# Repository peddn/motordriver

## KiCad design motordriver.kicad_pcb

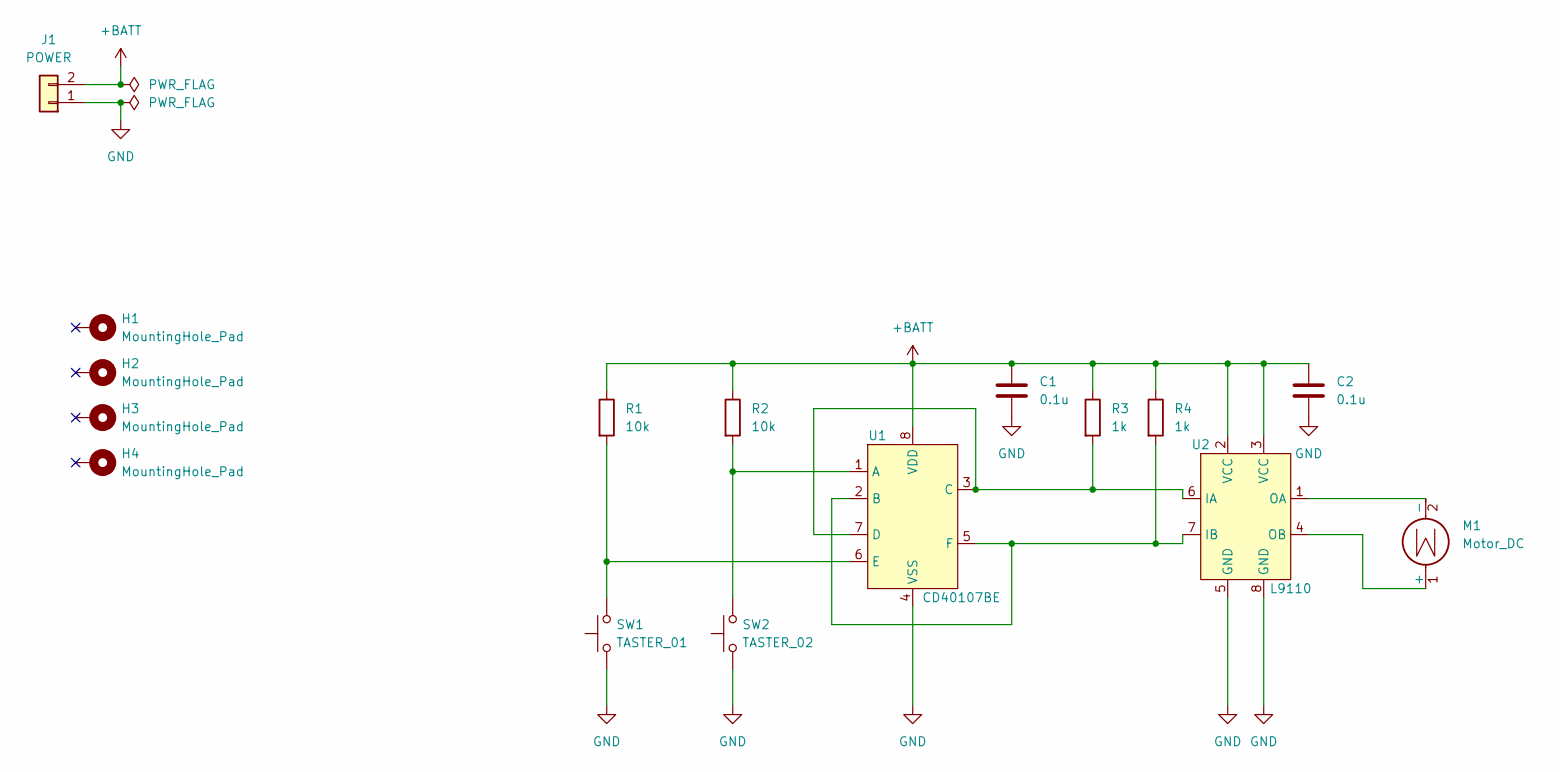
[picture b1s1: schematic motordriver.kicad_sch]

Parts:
C1, C2: 0.1u; C_1206_3216Metric
H1, H2, H3, H4: MountingHole_Pad; MountingHole_3.2mm_M3_Pad_Via
J1: POWER; JST_PH_B2B-PH-K_1x02_P2.00mm_Vertical
M1: Motor_DC; JST_PH_B2B-PH-K_1x02_P2.00mm_Vertical
R1, R2: 10k; R_1206_3216Metric
R3, R4: 1k; R_1206_3216Metric
SW1: TASTER_01; JST_PH_B2B-PH-K_1x02_P2.00mm_Vertical
SW2: TASTER_02; JST_PH_B2B-PH-K_1x02_P2.00mm_Vertical
U1: CD40107BE; DIP-8_W7.62mm_LongPads
U2: L9110; DIP-8_W7.62mm_LongPads

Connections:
+BATT: C1.1, C2.1, J1.2, R1.1, R2.1, R3.1, R4.1, U1.8 (VDD), U2.2 (VCC), U2.3 (VCC)
GND: C1.2, C2.2, J1.1, SW1.1, SW2.1, U1.4 (VSS), U2.5 (GND), U2.8 (GND)
unnamed: M1.1 (+), U2.4 (OB)
unnamed: M1.2 (-), U2.1 (OA)
unnamed: R1.2, SW1.2, U1.6 (E)
unnamed: R2.2, SW2.2, U1.1 (A)
unnamed: R3.2, U1.3 (C), U1.7 (D), U2.6 (IA)
unnamed: R4.2, U1.2 (B), U1.5 (F), U2.7 (IB)

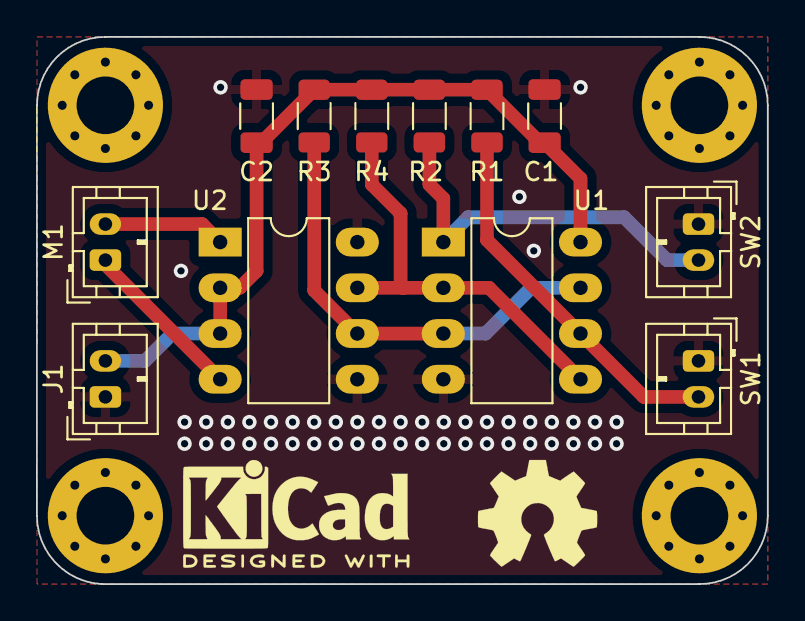
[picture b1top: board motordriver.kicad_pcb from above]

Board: 2 copper layers, 40.6 x 30.4 mm, 16 parts (0 on the bottom side), 8 nets.
